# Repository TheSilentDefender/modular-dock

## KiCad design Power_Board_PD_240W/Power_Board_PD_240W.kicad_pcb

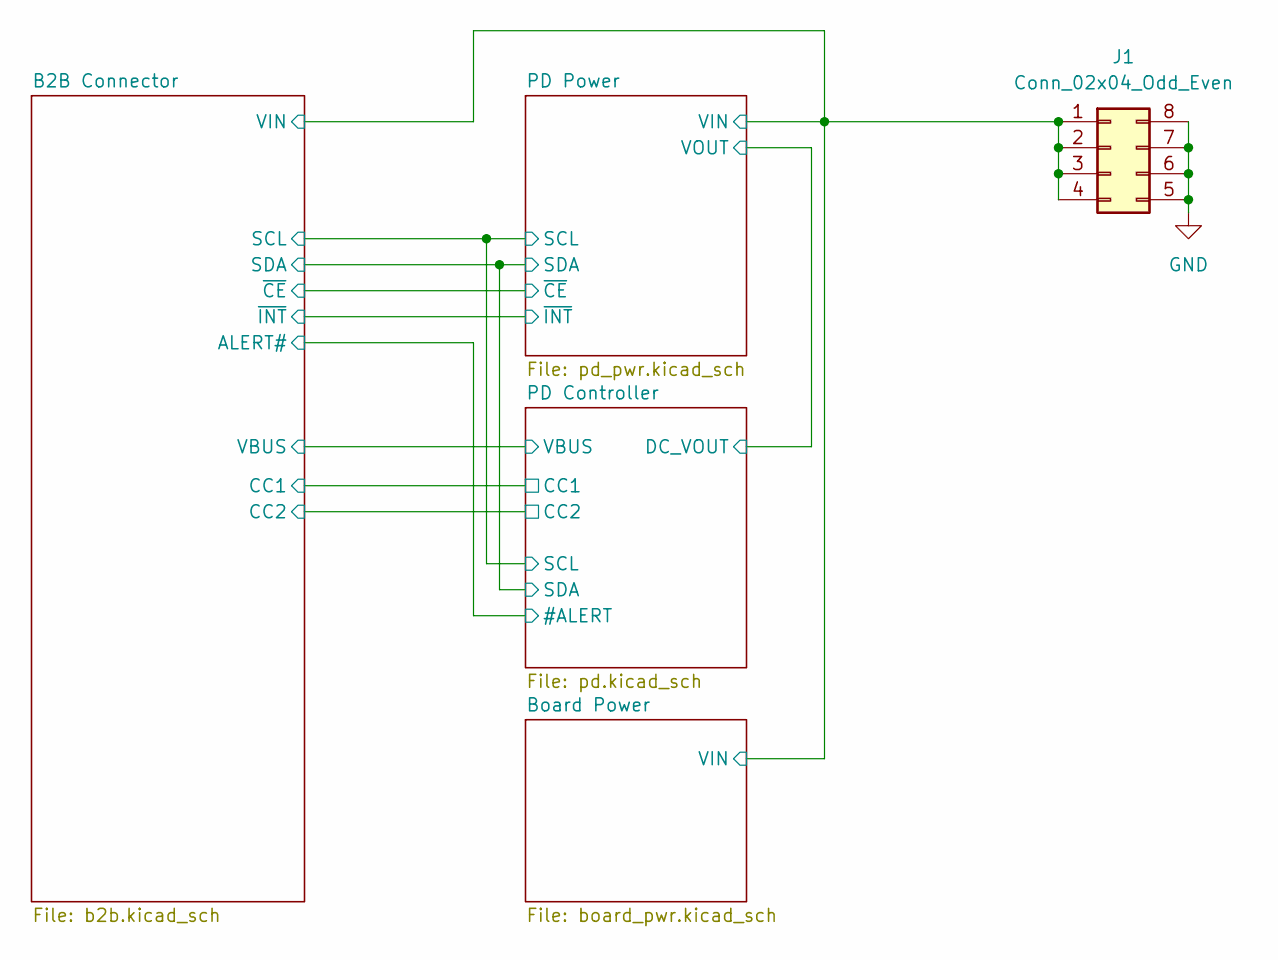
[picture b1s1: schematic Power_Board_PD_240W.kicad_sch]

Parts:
J1: Conn_02x04_Odd_Even; Molex_Mini-Fit_Jr_5569-08A2_2x04_P4.20mm_Horizontal

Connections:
/PD Power/VIN_CAP: J1.1, J1.2, J1.3, J1.4; also elsewhere on the board
GND: J1.5, J1.6, J1.7, J1.8; also elsewhere on the board

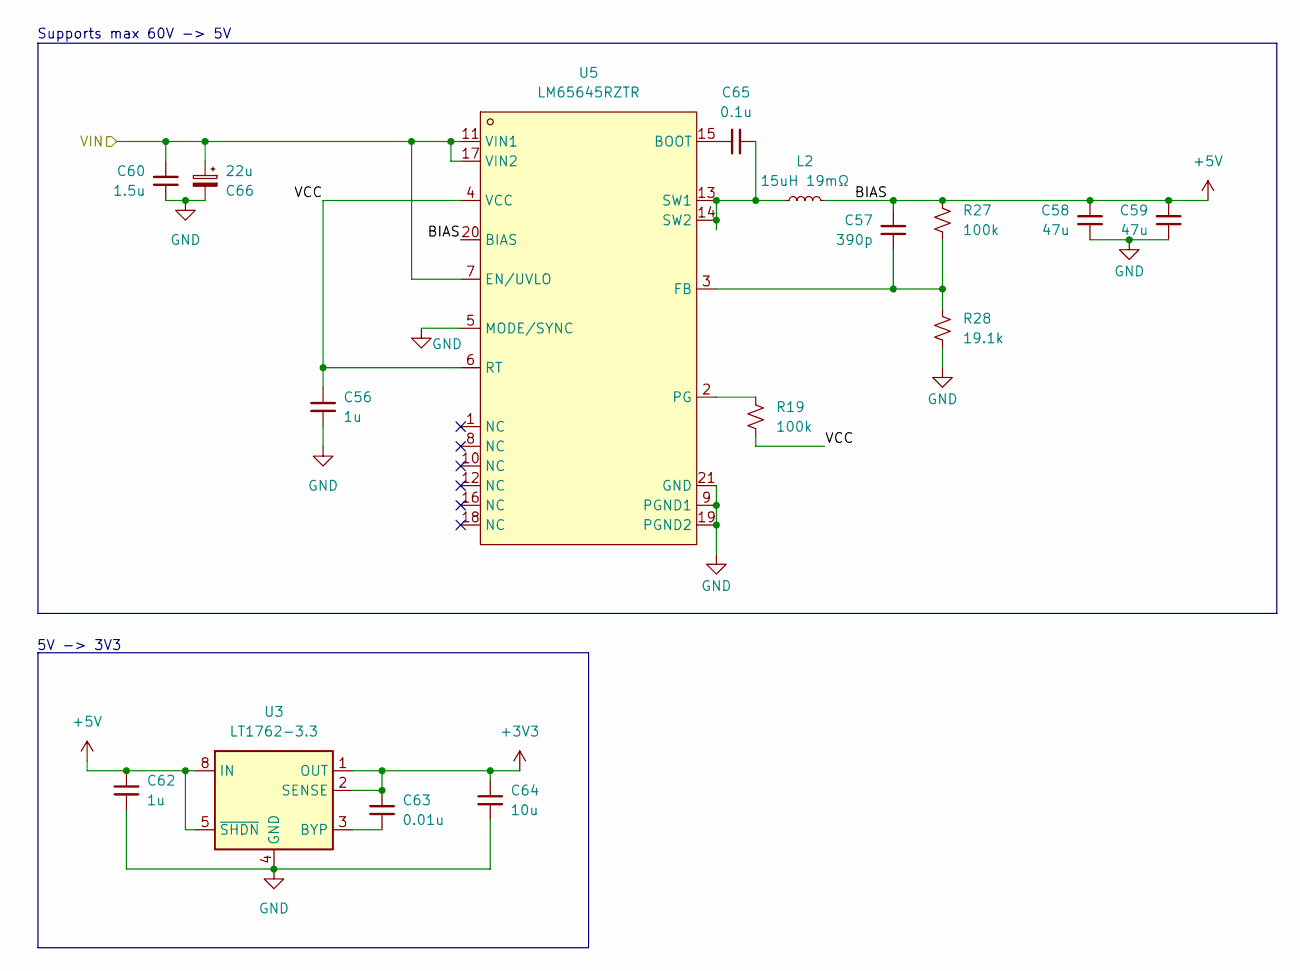
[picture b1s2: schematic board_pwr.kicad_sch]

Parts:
C56: 1u; C_1206_3216Metric
C57: 390p; C_0402_1005Metric
C58, C59: 47u; C_1210_3225Metric
C60: 1.5u; C_1812_4532Metric
C62: 1u; C_0402_1005Metric
C63: 0.01u; C_0402_1005Metric
C64: 10u; C_0603_1608Metric
C65: 0.1u; C_0402_1005Metric
C66: 22u; CP_Elec_10x10.5
L2: 15uH 19mΩ; L_Sunlord_SWRB1207S
R19, R27: 100k; R_0402_1005Metric
R28: 19.1k; R_0402_1005Metric
U3: LT1762-3.3; MSOP-8_3x3mm_P0.65mm
U5: LM65645RZTR; WQFN-FCRLF-20_L3.6-W2.6-P0.50-TL; MPN LM65645RZTR; LCSC Part C49256229

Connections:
+3V3: C63.1, C64.1, U3.1 (OUT), U3.2 (SENSE); also elsewhere on the board
+5V: C57.1, C58.1, C59.1, C62.1, L2.2, R27.1, U3.5 (~SHDN), U3.8 (IN), U5.20 (BIAS); also elsewhere on the board
/Board Power/VCC: C56.1, R19.2, U5.4 (VCC), U5.6 (RT)
/PD Power/VIN_CAP: C60.1, C66.1, U5.7 (EN/UVLO), U5.11 (VIN1), U5.17 (VIN2); also elsewhere on the board
GND: C56.2, C58.2, C59.2, C60.2, C62.2, C64.2, C66.2, R28.2, U3.4 (GND), U5.5 (MODE/SYNC), U5.9 (PGND1), U5.19 (PGND2), U5.21 (GND); also elsewhere on the board
unnamed: C63.2, U3.3 (BYP)
unnamed: C65.1, U5.15 (BOOT)
unnamed: C57.2, R27.2, R28.1, U5.3 (FB)
unnamed: R19.1, U5.2 (PG)
unnamed: C65.2, L2.1, U5.13 (SW1), U5.14 (SW2)

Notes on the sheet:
5V -> 3V3
Supports max 60V -> 5V

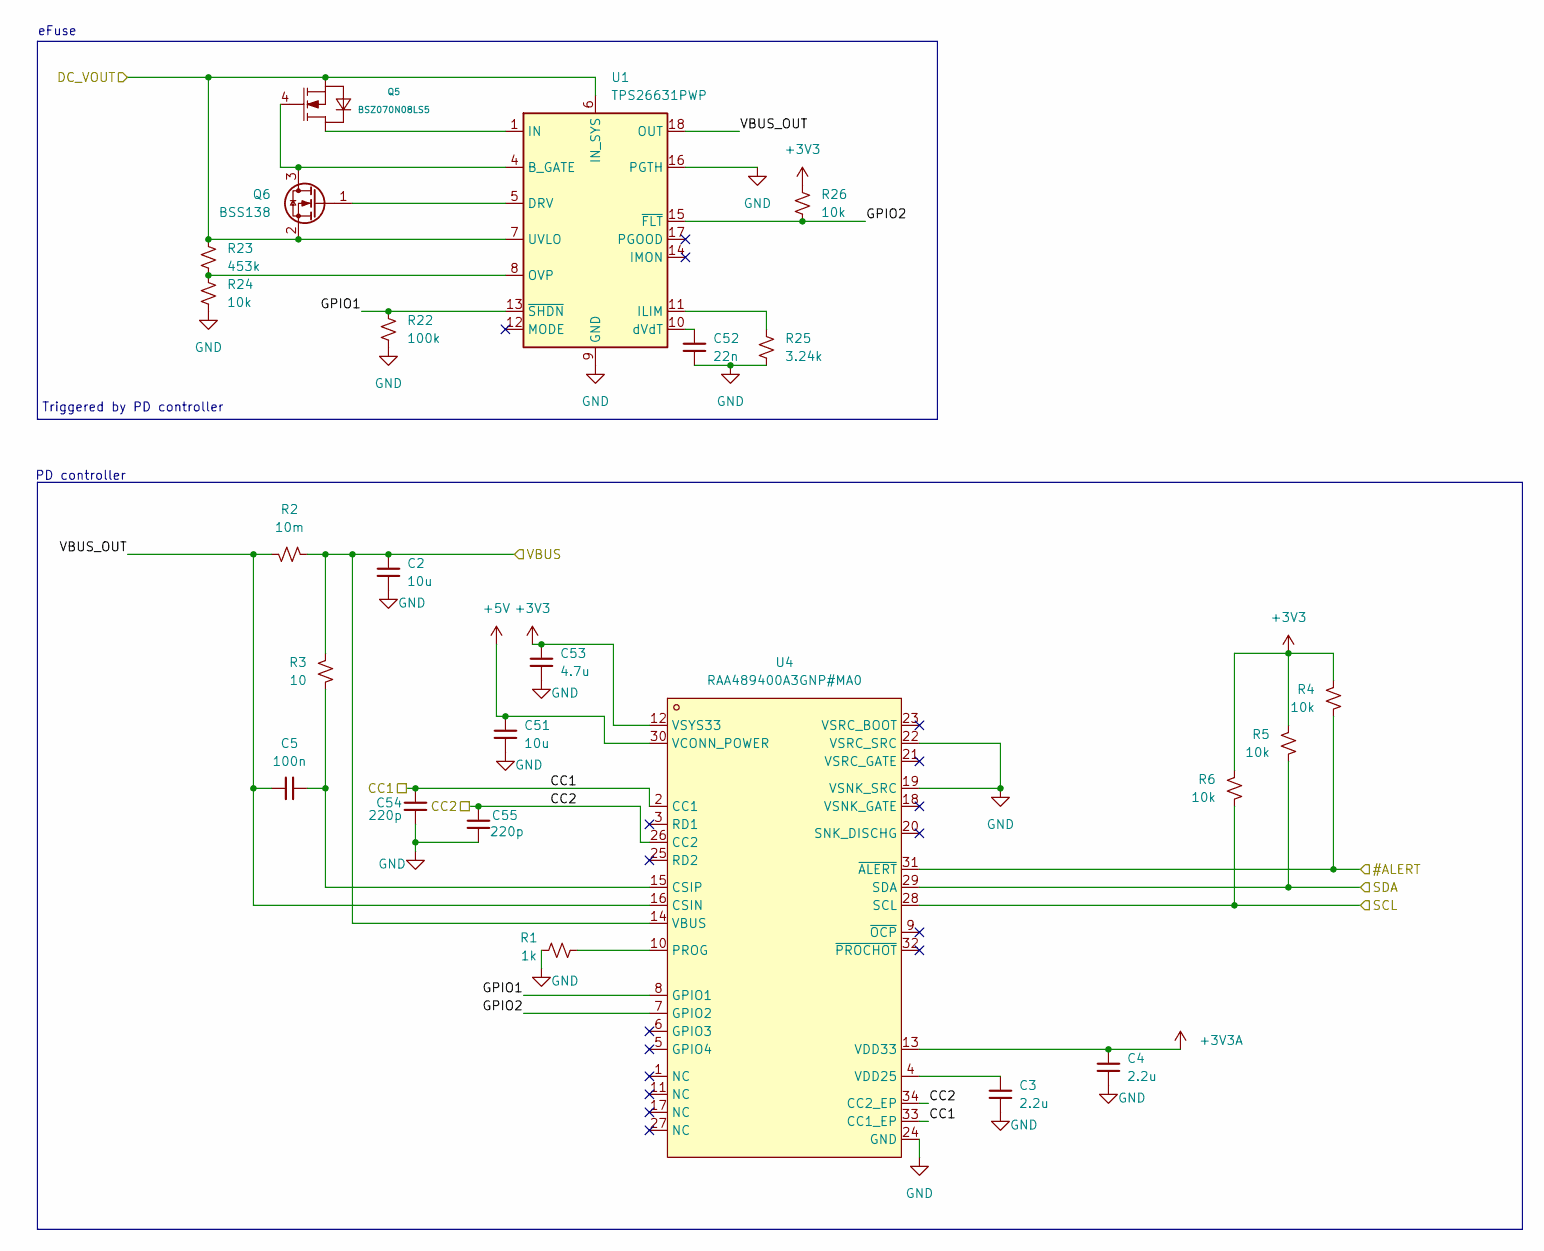
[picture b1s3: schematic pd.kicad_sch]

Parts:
C2: 10u; C_1210_3225Metric
C3, C4: 2.2u; C_0402_1005Metric
C5: 100n; C_0805_2012Metric
C51: 10u; C_0603_1608Metric
C52: 22n; C_0402_1005Metric
C53: 4.7u; C_0402_1005Metric
C54, C55: 220p; C_0402_1005Metric
Q5: BSZ070N08LS5
Q6: BSS138; SOT-23
R1: 1k; R_0402_1005Metric
R2: 10m; R_1206_3216Metric
R3: 10; R_0402_1005Metric
R4, R5, R6, R24, R26: 10k; R_0402_1005Metric
R22: 100k; R_0402_1005Metric
R23: 453k; R_0603_1608Metric
R25: 3.24k; R_0402_1005Metric
U1: TPS26631PWP; HTSSOP-20-1EP_4.4x6.5mm_P0.65mm_EP3.4x6.5mm_Mask2.96x2.96mm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
U4: RAA489400A3GNP#MA0; TQFN-32_L5.0-W3.0-P0.40-TL_RAA489400ARGNP; MPN RAA489400A3GNP#MA0; LCSC Part C43519750

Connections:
+3V3: C53.1, R4.2, R5.1, R6.1, R26.1, U4.12 (VSYS33); also elsewhere on the board
+3V3A: C4.1, U4.13 (VDD33)
+5V: C51.1, U4.30 (VCONN_POWER); also elsewhere on the board
/B2B Connector/ALERT#: R4.1, U4.31 (~ALERT); also elsewhere on the board
/B2B Connector/SCL: R6.2, U4.28 (SCL); also elsewhere on the board
/B2B Connector/SDA: R5.2, U4.29 (SDA); also elsewhere on the board
/B2B Connector/VBUS: C2.1, R2.2, R3.1, U4.14 (VBUS); also elsewhere on the board
/PD Controller/CC1: C54.1, U4.2 (CC1), U4.33 (CC1_EP); also elsewhere on the board
/PD Controller/CC2: C55.1, U4.26 (CC2), U4.34 (CC2_EP); also elsewhere on the board
/PD Controller/GPIO1: R22.1, U1.13 (~SHDN), U4.8 (GPIO1)
/PD Controller/GPIO2: R26.2, U1.15 (~FLT), U4.7 (GPIO2)
/PD Controller/VBUS_OUT: C5.1, R2.1, U1.18 (OUT), U1.19 (OUT), U1.20 (OUT), U4.16 (CSIN)
/PD Power/VOUT_CAP: Q5.1 (SOURCE), Q5.2 (SOURCE), Q5.3 (SOURCE), Q6.2 (S), R23.1, U1.6 (IN_SYS), U1.7 (UVLO); also elsewhere on the board
GND: C2.2, C3.2, C4.2, C51.2, C52.2, C53.2, C54.2, C55.2, R1.1, R22.2, R24.2, R25.2, U1.9 (GND), U1.16 (PGTH), U1.21 (GND), U4.19 (VSNK_SRC), U4.22 (VSRC_SRC), U4.24 (GND); also elsewhere on the board
unnamed: Q5.5 (DRAIN), Q5.6 (DRAIN), Q5.7 (DRAIN), Q5.8 (DRAIN), U1.1 (IN), U1.2 (IN), U1.3 (IN)
unnamed: Q5.4 (GATE), Q6.3 (D), U1.4 (B_GATE)
unnamed: Q6.1 (G), U1.5 (DRV)
unnamed: R25.1, U1.11 (ILIM)
unnamed: R23.2, R24.1, U1.8 (OVP)
unnamed: C52.1, U1.10 (dVdT)
unnamed: C5.2, R3.2, U4.15 (CSIP)
unnamed: R1.2, U4.10 (PROG)
unnamed: C3.1, U4.4 (VDD25)

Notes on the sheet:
Triggered by PD controller
PD controller
eFuse

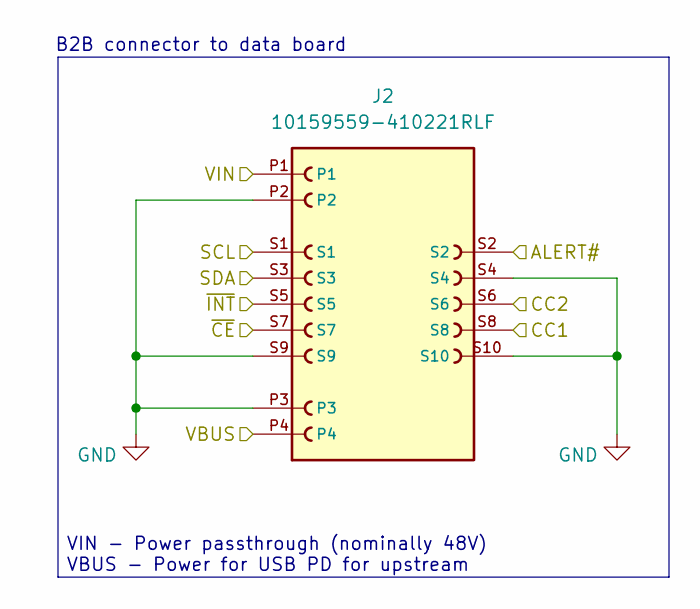
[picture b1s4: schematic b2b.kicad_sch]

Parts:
J2: 10159559-410221RLF; AMPHENOL_10159559-410221RLF; PARTREV D

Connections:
/B2B Connector/ALERT#: J2.S2; also elsewhere on the board
/B2B Connector/SCL: J2.S1; also elsewhere on the board
/B2B Connector/SDA: J2.S3; also elsewhere on the board
/B2B Connector/VBUS: J2.P4; also elsewhere on the board
/B2B Connector/~CE: J2.S7; also elsewhere on the board
/B2B Connector/~INT: J2.S5; also elsewhere on the board
/PD Controller/CC1: J2.S8; also elsewhere on the board
/PD Controller/CC2: J2.S6; also elsewhere on the board
/PD Power/VIN_CAP: J2.P1; also elsewhere on the board
GND: J2.P2, J2.P3, J2.S4, J2.S9, J2.S10; also elsewhere on the board

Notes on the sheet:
B2B connector to data board
VIN - Power passthrough (nominally 48V) VBUS - Power for USB PD for upstream

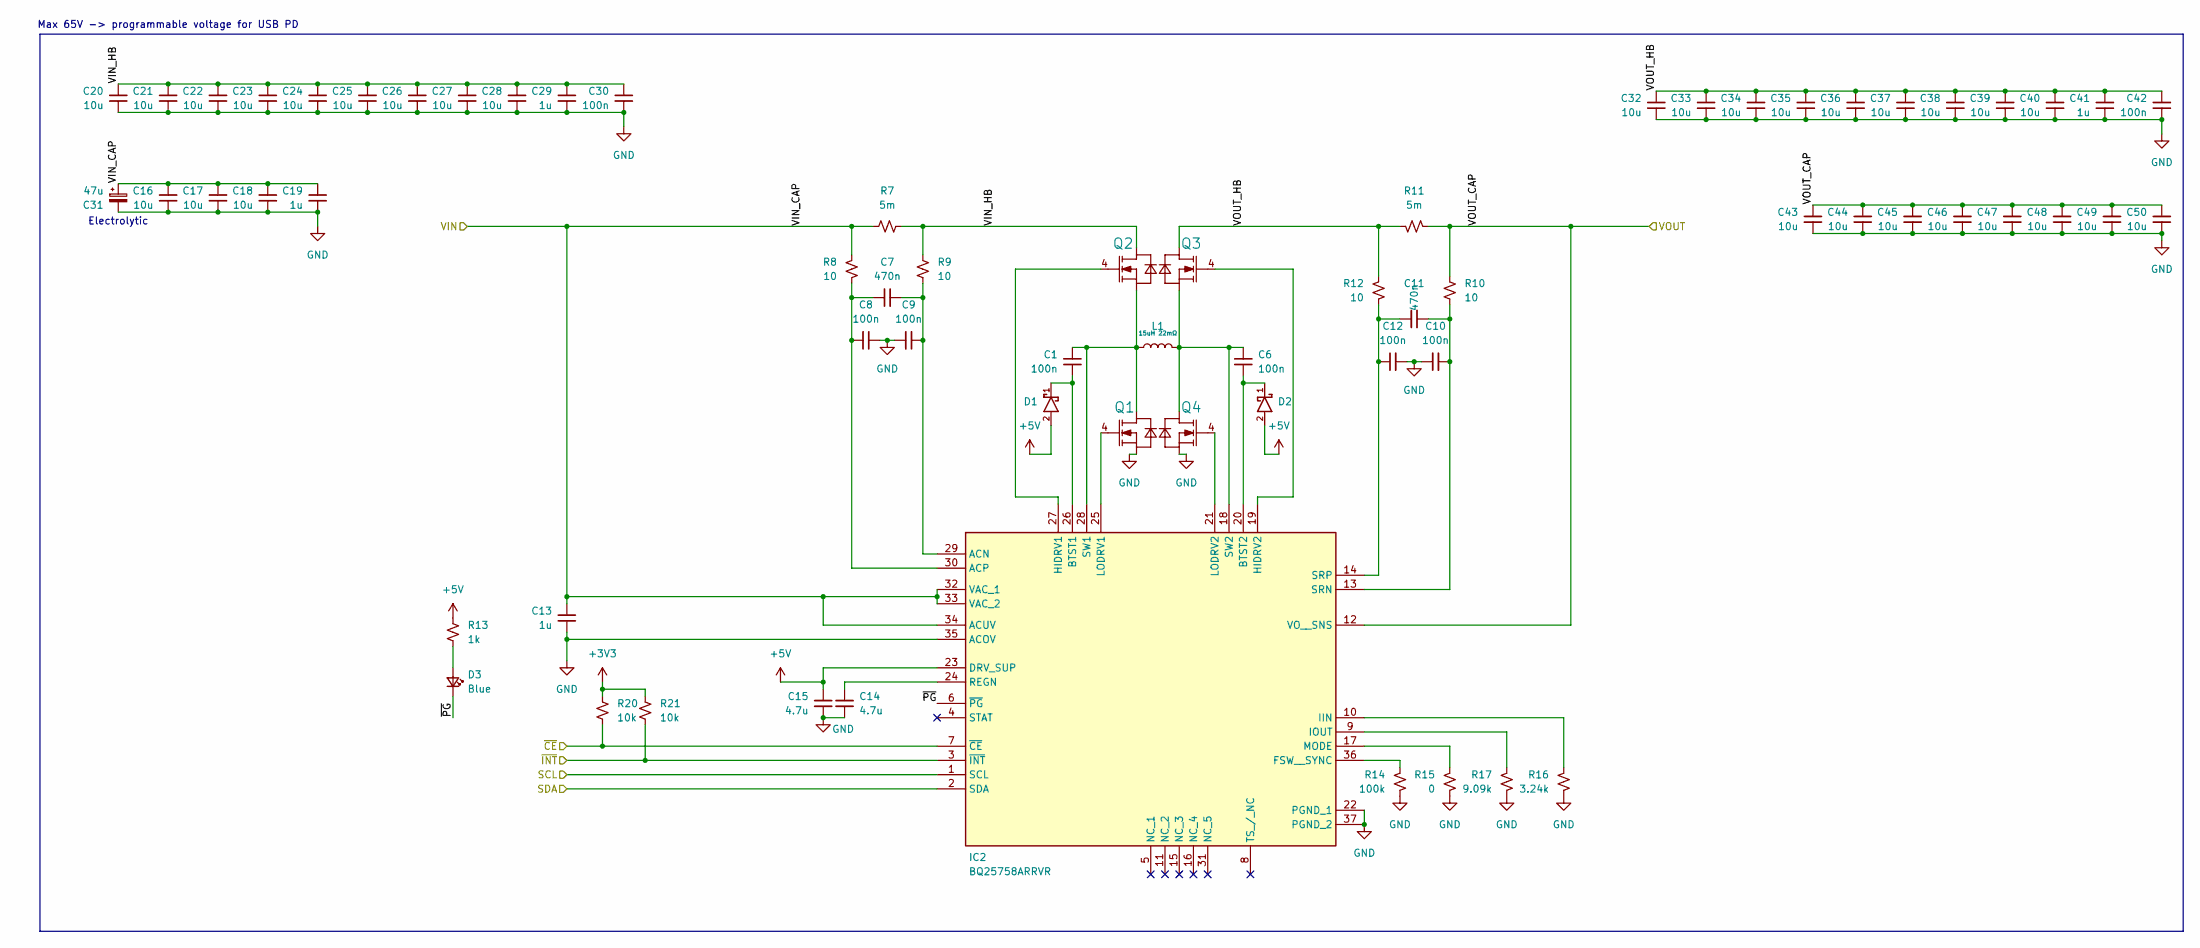
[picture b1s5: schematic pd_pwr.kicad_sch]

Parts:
C1, C6, C8, C9, C10, C12, C30, C42: 100n; C_0805_2012Metric
C7, C11: 470n; C_0805_2012Metric
C13, C19, C29, C41: 1u; C_1206_3216Metric
C14, C15: 4.7u; C_1210_3225Metric
C16, C17, C18, C20, C21, C22, C23, C24, C25, C26, C27, C28, C32, C33, C34, C35, C36, C37, C38, C39, C40, C43, C44, C45, C46, C47, C48, C49, C50: 10u; C_1210_3225Metric
C31: 47u; CP_Elec_10x10.5
D1, D2: NSR02100HT1G; SOD2512X110N; MOUSER_PART_NUMBER 863-NSR02100HT1G
D3: Blue; LED_0603_1608Metric
IC2: BQ25758ARRVR; QFN50P500X600X100-37N-D; Manufacturer_Part_Number BQ25758ARRVR
L1: 15uH 22mΩ; IND-SMD_L13.7-W12.6_MS1360
Q1, Q2, Q3, Q4: BSZ070N08LS5
R7, R11: 5m; R_1206_3216Metric
R8, R9, R10, R12: 10; R_0402_1005Metric
R13: 1k; R_0402_1005Metric
R14: 100k; R_0402_1005Metric
R15: 0; R_0603_1608Metric
R16: 3.24k; R_0402_1005Metric
R17: 9.09k; R_0402_1005Metric
R20, R21: 10k; R_0402_1005Metric

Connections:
+3V3: R20.2, R21.2; also elsewhere on the board
+5V: C15.2, D1.2, D2.2, IC2.23 (DRV_SUP), R13.2; also elsewhere on the board
/B2B Connector/SCL: IC2.1 (SCL); also elsewhere on the board
/B2B Connector/SDA: IC2.2 (SDA); also elsewhere on the board
/B2B Connector/~CE: IC2.7 (~CE), R20.1; also elsewhere on the board
/B2B Connector/~INT: IC2.3 (~INT), R21.1; also elsewhere on the board
/PD Power/VIN_CAP: C13.2, C16.2, C17.2, C18.2, C19.2, C31.1, IC2.32 (VAC_1), IC2.33 (VAC_2), IC2.34 (ACUV), R7.1, R8.2; also elsewhere on the board
/PD Power/VIN_HB: C20.2, C21.2, C22.2, C23.2, C24.2, C25.2, C26.2, C27.2, C28.2, C29.2, C30.2, Q2.5 (DRAIN), Q2.6 (DRAIN), Q2.7 (DRAIN), Q2.8 (DRAIN), R7.2, R9.2
/PD Power/VOUT_CAP: C43.2, C44.2, C45.2, C46.2, C47.2, C48.2, C49.2, C50.2, IC2.12 (VO__SNS), R10.2, R11.1; also elsewhere on the board
/PD Power/VOUT_HB: C32.2, C33.2, C34.2, C35.2, C36.2, C37.2, C38.2, C39.2, C40.2, C41.2, C42.2, Q3.5 (DRAIN), Q3.6 (DRAIN), Q3.7 (DRAIN), Q3.8 (DRAIN), R11.2, R12.2
/PD Power/~PG: D3.1 (K), IC2.6 (~PG)
GND: C8.2, C9.1, C10.2, C12.1, C13.1, C14.1, C15.1, C16.1, C17.1, C18.1, C19.1, C20.1, C21.1, C22.1, C23.1, C24.1, C25.1, C26.1, C27.1, C28.1, C29.1, C30.1, C31.2, C32.1, C33.1, C34.1, C35.1, C36.1, C37.1, C38.1, C39.1, C40.1, C41.1, C42.1, C43.1, C44.1, C45.1, C46.1, C47.1, C48.1, C49.1, C50.1, IC2.22 (PGND_1), IC2.35 (ACOV), IC2.37 (PGND_2), Q1.1 (SOURCE), Q1.2 (SOURCE), Q1.3 (SOURCE), Q4.1 (SOURCE), Q4.2 (SOURCE), Q4.3 (SOURCE), R14.1, R15.1, R16.1, R17.1; also elsewhere on the board
unnamed: D3.2 (A), R13.1
unnamed: C7.2, C9.2, IC2.29 (ACN), R9.1
unnamed: C7.1, C8.1, IC2.30 (ACP), R8.1
unnamed: C1.2, D1.1, IC2.26 (BTST1)
unnamed: C6.2, D2.1, IC2.20 (BTST2)
unnamed: IC2.36 (FSW__SYNC), R14.2
unnamed: IC2.27 (HIDRV1), Q2.4 (GATE)
unnamed: IC2.19 (HIDRV2), Q3.4 (GATE)
unnamed: IC2.10 (IIN), R16.2
unnamed: IC2.9 (IOUT), R17.2
unnamed: IC2.25 (LODRV1), Q1.4 (GATE)
unnamed: IC2.21 (LODRV2), Q4.4 (GATE)
unnamed: IC2.17 (MODE), R15.2
unnamed: C14.2, IC2.24 (REGN)
unnamed: C10.1, C11.1, IC2.13 (SRN), R10.1
unnamed: C11.2, C12.2, IC2.14 (SRP), R12.1
unnamed: C1.1, IC2.28 (SW1), L1.1, Q1.5 (DRAIN), Q1.6 (DRAIN), Q1.7 (DRAIN), Q1.8 (DRAIN), Q2.1 (SOURCE), Q2.2 (SOURCE), Q2.3 (SOURCE)
unnamed: C6.1, IC2.18 (SW2), L1.2, Q3.1 (SOURCE), Q3.2 (SOURCE), Q3.3 (SOURCE), Q4.5 (DRAIN), Q4.6 (DRAIN), Q4.7 (DRAIN), Q4.8 (DRAIN)

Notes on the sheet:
Max 65V -> programmable voltage for USB PD
Electrolytic

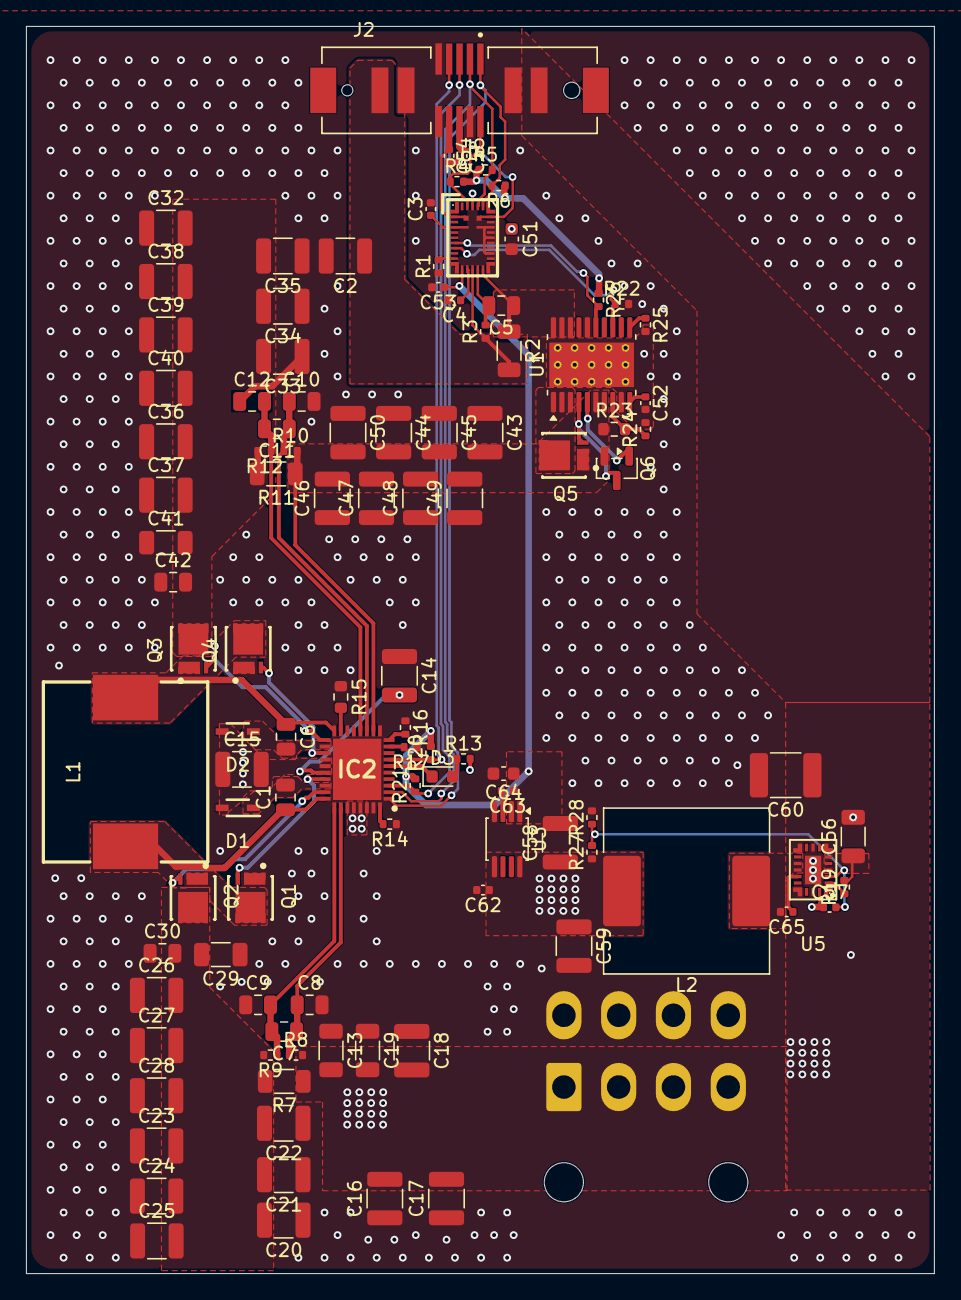
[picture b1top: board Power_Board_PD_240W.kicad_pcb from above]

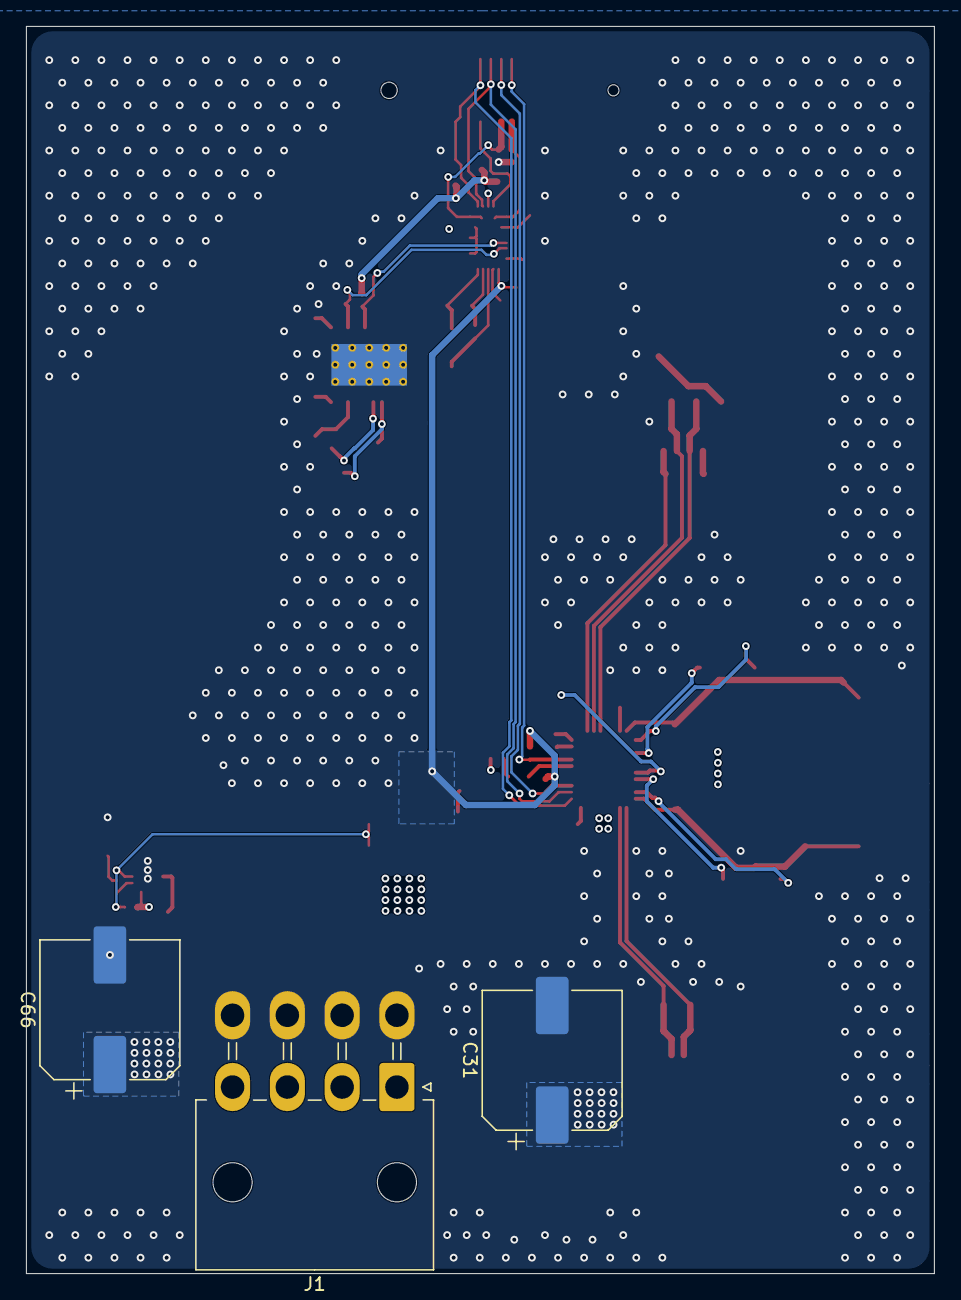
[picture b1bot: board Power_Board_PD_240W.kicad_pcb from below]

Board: 4 copper layers, 69.6 x 95.6 mm, 110 parts (3 on the bottom side), 53 nets.
